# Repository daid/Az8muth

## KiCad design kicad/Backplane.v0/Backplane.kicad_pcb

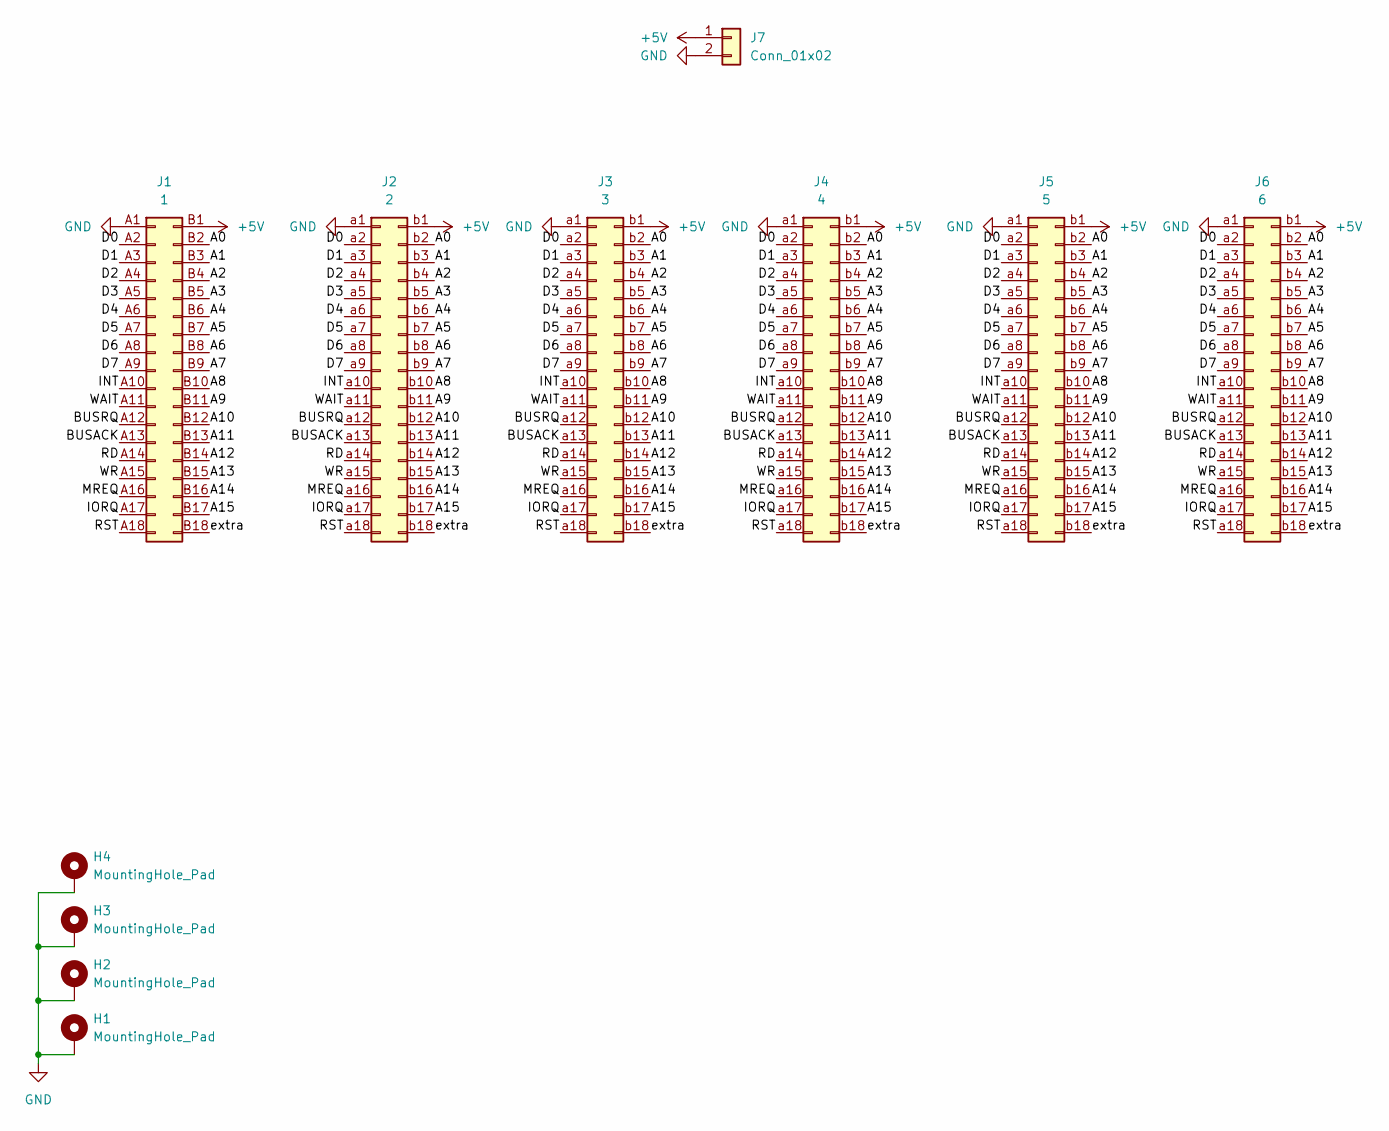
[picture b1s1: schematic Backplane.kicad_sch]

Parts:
H1, H2, H3, H4: MountingHole_Pad; MountingHole_3.2mm_M3_Pad
J1: 1; BUS_PCIexpress_x1
J2: 2; PCI-E36P
J3: 3; PCI-E36P
J4: 4; PCI-E36P
J5: 5; PCI-E36P
J6: 6; PCI-E36P
J7: Conn_01x02; PinHeader_2x01_P2.54mm_Vertical

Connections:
+5V: J1.B1 (Pin_b1), J2.b1, J3.b1, J4.b1, J5.b1, J6.b1, J7.1
/A0: J1.B2 (Pin_b2), J2.b2, J3.b2, J4.b2, J5.b2, J6.b2
/A1: J1.B3 (Pin_b3), J2.b3, J3.b3, J4.b3, J5.b3, J6.b3
/A2: J1.B4 (Pin_b4), J2.b4, J3.b4, J4.b4, J5.b4, J6.b4
/A3: J1.B5 (Pin_b5), J2.b5, J3.b5, J4.b5, J5.b5, J6.b5
/A4: J1.B6 (Pin_b6), J2.b6, J3.b6, J4.b6, J5.b6, J6.b6
/A5: J1.B7 (Pin_b7), J2.b7, J3.b7, J4.b7, J5.b7, J6.b7
/A6: J1.B8 (Pin_b8), J2.b8, J3.b8, J4.b8, J5.b8, J6.b8
/A7: J1.B9 (Pin_b9), J2.b9, J3.b9, J4.b9, J5.b9, J6.b9
/A8: J1.B10 (Pin_b10), J2.b10, J3.b10, J4.b10, J5.b10, J6.b10
/A9: J1.B11 (Pin_b11), J2.b11, J3.b11, J4.b11, J5.b11, J6.b11
/A10: J1.B12 (Pin_b12), J2.b12, J3.b12, J4.b12, J5.b12, J6.b12
/A11: J1.B13 (Pin_b13), J2.b13, J3.b13, J4.b13, J5.b13, J6.b13
/A12: J1.B14 (Pin_b14), J2.b14, J3.b14, J4.b14, J5.b14, J6.b14
/A13: J1.B15 (Pin_b15), J2.b15, J3.b15, J4.b15, J5.b15, J6.b15
/A14: J1.B16 (Pin_b16), J2.b16, J3.b16, J4.b16, J5.b16, J6.b16
/A15: J1.B17 (Pin_b17), J2.b17, J3.b17, J4.b17, J5.b17, J6.b17
/BUSACK: J1.A13 (Pin_a13), J2.a13, J3.a13, J4.a13, J5.a13, J6.a13
/BUSRQ: J1.A12 (Pin_a12), J2.a12, J3.a12, J4.a12, J5.a12, J6.a12
/D0: J1.A2 (Pin_a2), J2.a2, J3.a2, J4.a2, J5.a2, J6.a2
/D1: J1.A3 (Pin_a3), J2.a3, J3.a3, J4.a3, J5.a3, J6.a3
/D2: J1.A4 (Pin_a4), J2.a4, J3.a4, J4.a4, J5.a4, J6.a4
/D3: J1.A5 (Pin_a5), J2.a5, J3.a5, J4.a5, J5.a5, J6.a5
/D4: J1.A6 (Pin_a6), J2.a6, J3.a6, J4.a6, J5.a6, J6.a6
/D5: J1.A7 (Pin_a7), J2.a7, J3.a7, J4.a7, J5.a7, J6.a7
/D6: J1.A8 (Pin_a8), J2.a8, J3.a8, J4.a8, J5.a8, J6.a8
/D7: J1.A9 (Pin_a9), J2.a9, J3.a9, J4.a9, J5.a9, J6.a9
/INT: J1.A10 (Pin_a10), J2.a10, J3.a10, J4.a10, J5.a10, J6.a10
/IORQ: J1.A17 (Pin_a17), J2.a17, J3.a17, J4.a17, J5.a17, J6.a17
/MREQ: J1.A16 (Pin_a16), J2.a16, J3.a16, J4.a16, J5.a16, J6.a16
/RD: J1.A14 (Pin_a14), J2.a14, J3.a14, J4.a14, J5.a14, J6.a14
/RST: J1.A18 (Pin_a18), J2.a18, J3.a18, J4.a18, J5.a18, J6.a18
/WAIT: J1.A11 (Pin_a11), J2.a11, J3.a11, J4.a11, J5.a11, J6.a11
/WR: J1.A15 (Pin_a15), J2.a15, J3.a15, J4.a15, J5.a15, J6.a15
/extra: J1.B18 (Pin_b18), J2.b18, J3.b18, J4.b18, J5.b18, J6.b18
GND: H1.1, H2.1, H3.1, H4.1, J1.A1 (Pin_a1), J2.a1, J3.a1, J4.a1, J5.a1, J6.a1, J7.2

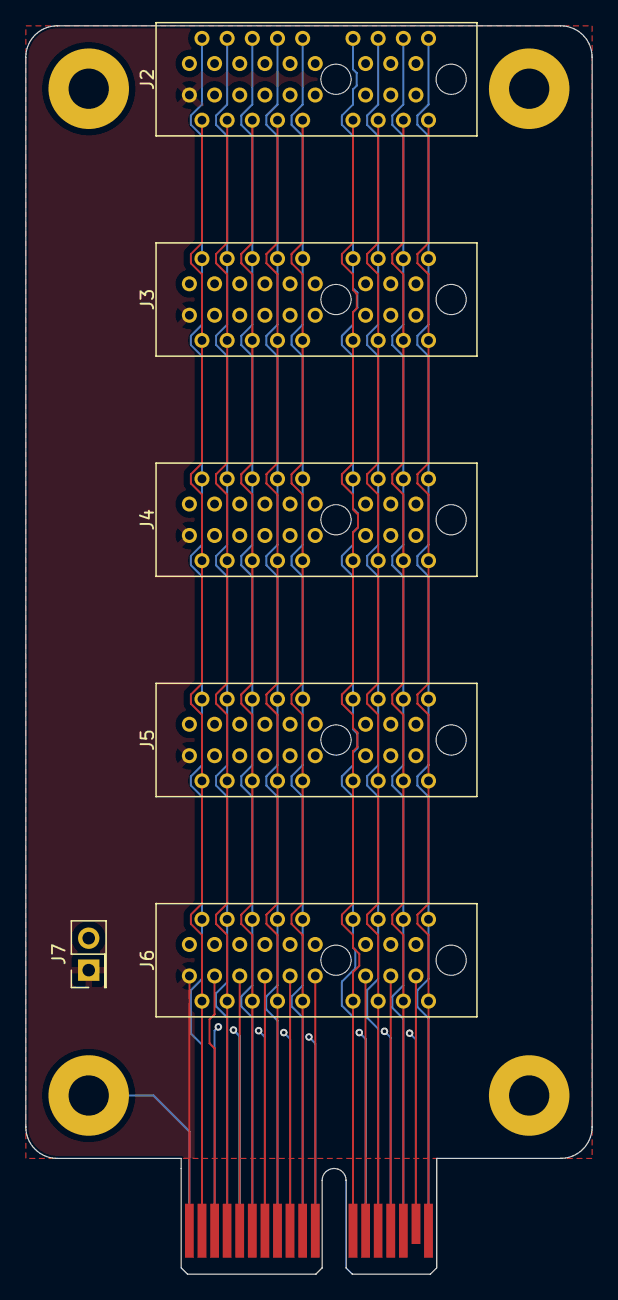
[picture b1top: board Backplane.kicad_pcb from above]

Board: 4 copper layers, 45.0 x 99.2 mm, 11 parts (0 on the bottom side), 36 nets.

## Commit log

2025-07-15 Backplane
